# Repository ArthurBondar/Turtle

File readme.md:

# Underwater Camera Project
Underwater Point of View Camera is designed for marine data collection applications. The primary goal of this project is to aid fisheries and biologist with underwater video collection.

## Features:
* 300m dept rated enclosure
* HD (1080p 30fps) video recording
* GPS location tracking
* 3-5 days battery run time ( 8hr recording per day )
* Ability to interface with various sensors

### Underwater Camera
This unit is designed to use as Point-of-view camera tag for Leatherback turtle studies. The unit features a GPS and a small power-efficient computer. The collected is stored on a microSD card.

### Line Camera
This unit is designed for stationary monitoring application used by fisheries. GPS module is optional for this system. The collected data is stored on a USB flash drive.

### Software Tools
Windows Programs for working with the unit:
* FFMPEG YAG - software for converting cameras native h264 video format to mp4
* Win32 Disk Imager - program for reading and writiing software to the unit

### System Images
Software packages are avaiable on Google Drive:
* Underwater / Line Camera Software Image: https://drive.google.com/file/d/10pP7cINGF-45ElwvxjcI6ze0uSWwasvH/view?usp=sharing

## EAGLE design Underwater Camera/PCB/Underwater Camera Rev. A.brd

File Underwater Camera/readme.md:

## Underwater Camera

### Overview
Underwater Camera Tag is designed for marine data collection. This device can be used as
a POV tag for aquatic turtles. The main interface for the system is a removable USB-flash drive. The on-board computer reads the drive during boot and stores all recorded data on it. During long deployments, more than one day, the Tag is designed to enter sleep mode to extend battery life.

### Operation
During deployment, the Tags computer records video and GPS location at daytime. The main computer shuts down for night-time operation to extend battery life. Recording cycles are handled by a separate microcontroller. Video files, GPS readings, and log file are stored on a removable USB flash drive.

### Main components
* Raspberry Pi + PiCamera 1080p30
* Arduino ProMini (Atmega328)
* Battery Bank + Charger/Boost
* Custom 3D printed parts
* Custom made PCB

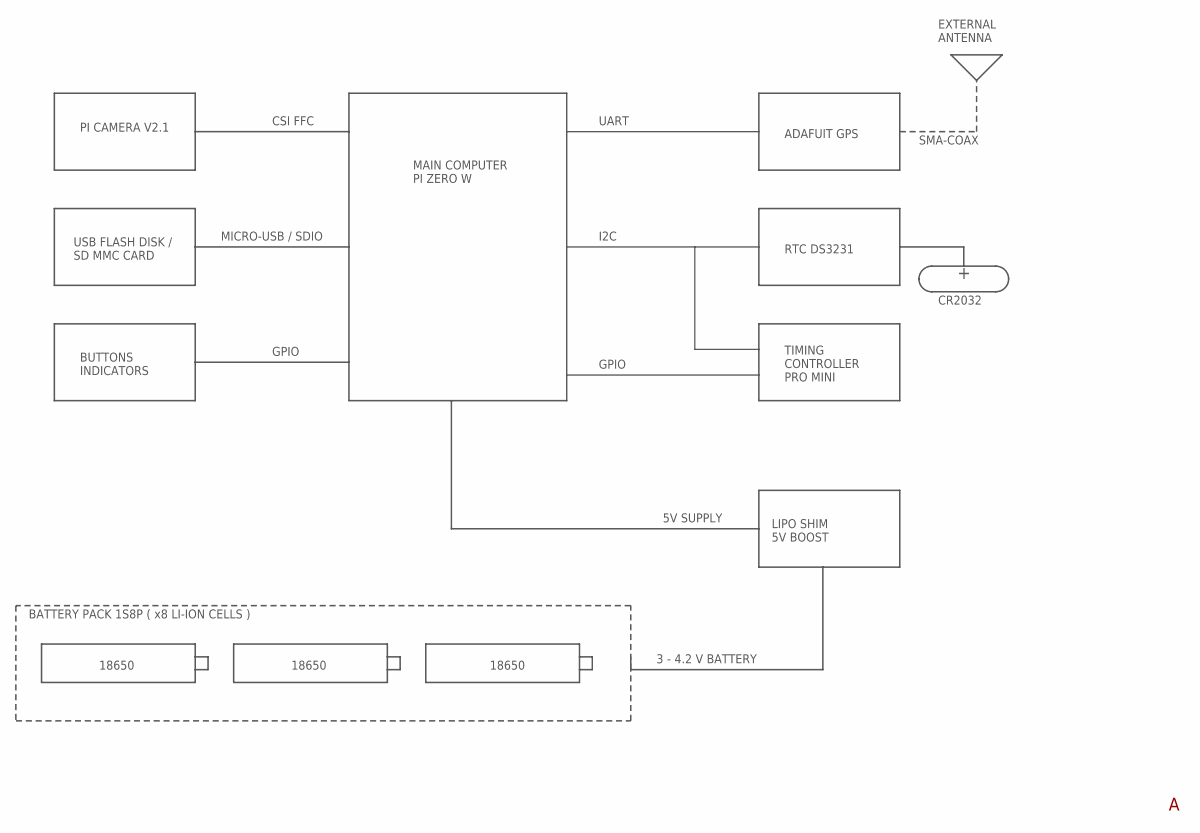
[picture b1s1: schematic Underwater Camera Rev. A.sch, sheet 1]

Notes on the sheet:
BATTERY PACK 1S8P ( x8 LI-ION CELLS )
LIPO SHIM 5V BOOST
MAIN COMPUTER PI ZERO W
TIMING CONTROLLER PRO MINI
PI CAMERA V2.1
USB FLASH DISK / SD MMC CARD
BUTTONS INDICATORS
ADAFUIT GPS
RTC DS3231
GPIO
5V SUPPLY
3 - 4.2 V BATTERY
SMA-COAX
EXTERNAL ANTENNA
18650
CR2032
MICRO-USB / SDIO
CSI FFC
I2C
UART

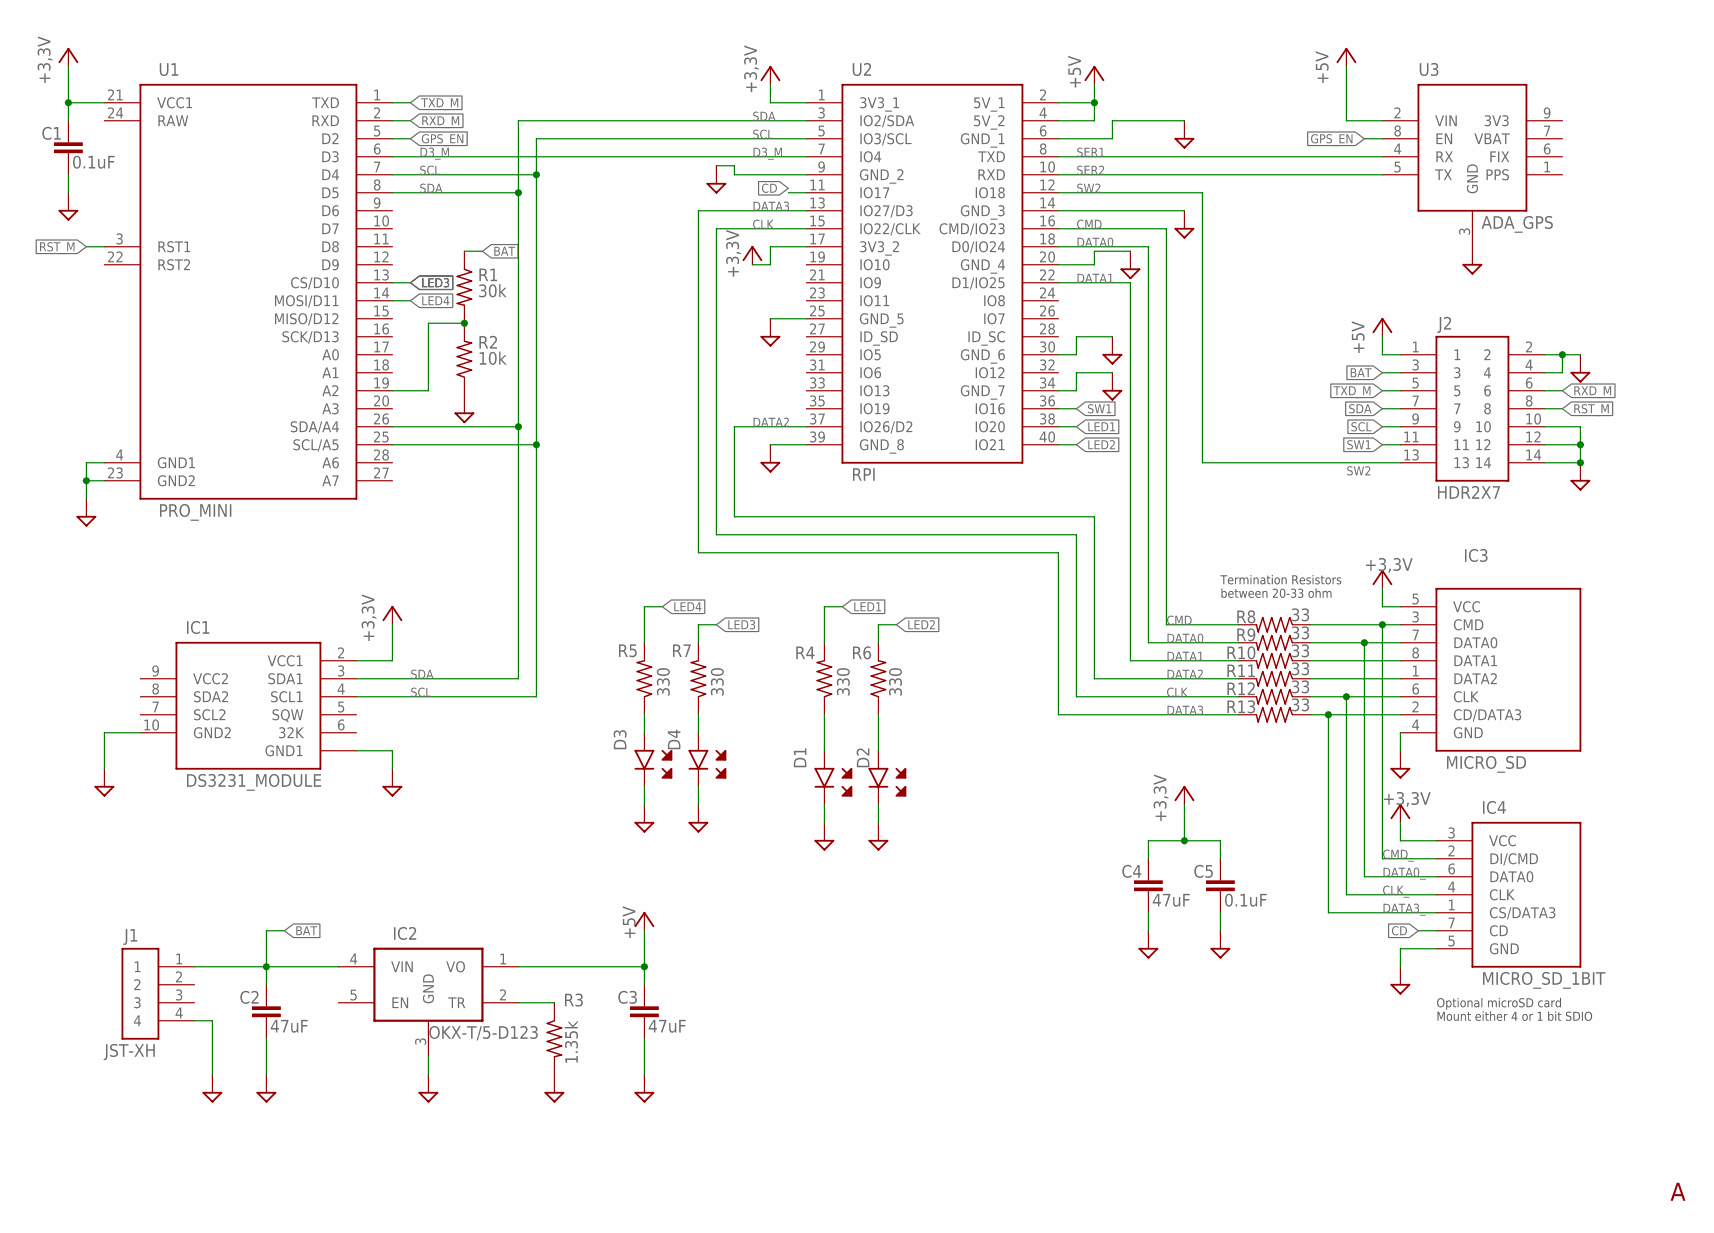
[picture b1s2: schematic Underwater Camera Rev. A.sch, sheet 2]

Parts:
C1, C5: 0.1uF; CAPPRD254W65D300H300B
C2, C3, C4: 47uF; CAPPRD508W65D1000H1100B
D1, D2, D3, D4: LED_THLED-2.54; LEDRD254W60D565H860B
IC1: DS3231_MODULE
IC2: OKX-T/5-D123; OKX-T/5-D12
IC3: MICRO_SD; MICRO_SD_SDIO
IC4: MICRO_SD_1BIT; MICRO_SD_SDIO1B
J1: JST-XH; HDR1X4
J2: HDR2X7
R1: 30k; RESAD1176W63L850D250B
R2: 10k; RESAD1176W63L850D250B
R3: 1.35k; RESAD1176W63L850D250B
R4, R5, R6, R7: 330; RESAD1176W63L850D250B
R8, R9, R10, R11, R12, R13: 33; RESAD1176W63L850D250B
U1: PRO_MINI
U2: RPI; PI_ZERO_W
U3: ADA_GPS; ADA_ULTIMATE_GPS

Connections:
+3,3V: C1.1, C4.1, C5.1, IC1.2 (VCC1), IC3.5 (VCC), IC4.3 (VCC), U1.21 (VCC1), U2.1 (3V3_1), U2.17 (3V3_2)
+5V: C3.1, IC2.1 (VO), J2.1, U2.2 (5V_1), U2.4 (5V_2), U3.2 (VIN)
BAT: C2.1, IC2.4 (VIN), J1.1, J2.3, R1.1
BAT_IN: R1.2, R2.2, U1.19 (A2)
CD: IC4.7 (CD), U2.11 (IO17)
CLK: R12.2, U2.15 (IO22/CLK)
CLK_: IC3.6 (CLK), IC4.4 (CLK), R12.1
CMD: R8.2, U2.16 (CMD/IO23)
CMD_: IC3.3 (CMD), IC4.2 (DI/CMD), R8.1
D3_M: U1.6 (D3), U2.7 (IO4)
DATA0: R9.2, U2.18 (D0/IO24)
DATA0_: IC3.7 (DATA0), IC4.6 (DATA0), R9.1
DATA1: R10.2, U2.22 (D1/IO25)
DATA1_: IC3.8 (DATA1), R10.1
DATA2: R11.2, U2.37 (IO26/D2)
DATA2_: IC3.1 (DATA2), R11.1
DATA3: R13.2, U2.13 (IO27/D3)
DATA3_: IC3.2 (CD/DATA3), IC4.1 (CS/DATA3), R13.1
GND: C1.2, C2.2, C3.2, C4.2, C5.2, D1.2, D2.2, D3.2, D4.2, IC1.1 (GND1), IC1.10 (GND2), IC2.3 (GND), IC3.4 (GND), IC4.5 (GND), J1.4, J2.2, J2.4, J2.10, J2.12, J2.14, R2.1, R3.2, U1.4 (GND1), U1.23 (GND2), U2.6 (GND_1), U2.9 (GND_2), U2.14 (GND_3), U2.20 (GND_4), U2.25 (GND_5), U2.30 (GND_6), U2.34 (GND_7), U2.39 (GND_8), U3.3 (GND)
GPS_EN: U1.5 (D2), U3.8 (EN)
LED1: R4.2, U2.38 (IO20)
LED2: R6.2, U2.40 (IO21)
LED3: R7.2, U1.13 (CS/D10)
LED4: R5.2, U1.14 (MOSI/D11)
unnamed: D4.1, R7.1
unnamed: IC2.2 (TR), R3.1
unnamed: D1.1, R4.1
unnamed: D2.1, R6.1
unnamed: D3.1, R5.1
RST_M: J2.8, U1.3 (RST1)
RXD_M: J2.6, U1.2 (RXD)
SCL: IC1.4 (SCL1), J2.9, U1.7 (D4), U1.25 (SCL/A5), U2.5 (IO3/SCL)
SDA: IC1.3 (SDA1), J2.7, U1.8 (D5), U1.26 (SDA/A4), U2.3 (IO2/SDA)
SER1: U2.8 (TXD), U3.4 (RX)
SER2: U2.10 (RXD), U3.5 (TX)
SW1: J2.11, U2.36 (IO16)
SW2: J2.13, U2.12 (IO18)
TXD_M: J2.5, U1.1 (TXD)

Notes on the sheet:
Termination Resistors between 20-33 ohm
Optional microSD card Mount either 4 or 1 bit SDIO

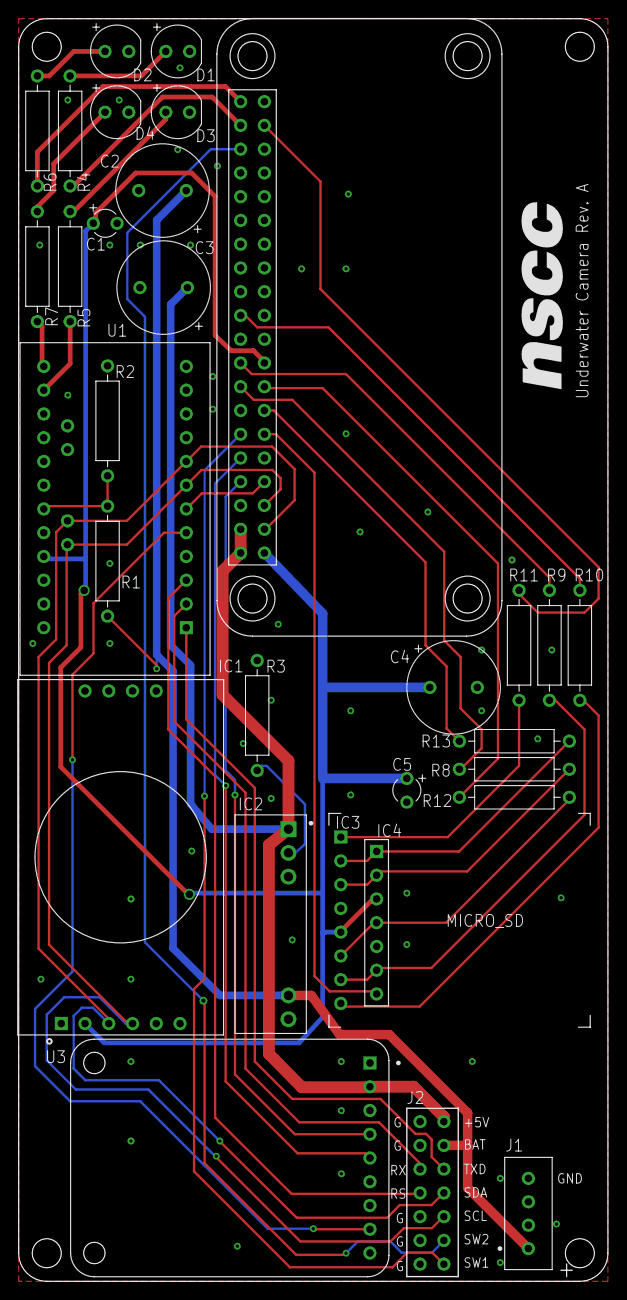
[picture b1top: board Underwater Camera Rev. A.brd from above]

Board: 2 copper layers, 63.0 x 135.0 mm, 31 parts (1 on the bottom side), 38 nets.

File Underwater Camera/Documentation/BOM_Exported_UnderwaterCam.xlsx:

Qty | Value | Device | Parts | Description
2 | 0.1uF | CAP_THCAP-TH-2MM | C1, C5 | Capacitor Electro. TH
1 | 1.35k | RES_THRES-D8.5 | R3 | Resistor TH
1 | 10k | RES_THRES-D8.5 | R2 | Resistor TH
1 | 30k | RES_THRES-D8.5 | R1 | Resistor TH
6 | 33 | RES_THRES-D8.5 | R8, R9, R10, R11, R12, R13 | Resistor TH
4 | 330 | RES_THRES-D8.5 | R4, R5, R6, R7 | Resistor TH
3 | 47uF | CAP_THCAP-ELECTRO-5.08 | C2, C3, C4 | Capacitor Electro. TH
1 | ADA_GPS | ADA_ULTIMATE_GPS9P_BREAKOUT | U3 | Ultimate GPS from Adafruit - Breakout
1 | DS3231_MODULE | DS3231_MODULE | IC1 | DS3231 RTC Breakout Module
1 | HDR2X7 | HDR2X7HDR2X7 | J2
1 | JST-XH | HDR1X4JST-XH | J1 | HEADER 1x4
4 | LED_THLED-2.54 | LED_THLED-2.54 | D1, D2, D3, D4 | TH LED - large
1 | MICRO_SD | MICRO_SD_SNIFFER | IC3 | SparkFun microSD sniffer - breaks out SDIO interface
1 | MICRO_SD_1BIT | MICRO_SD | IC4 | Sparkfun microSD Breakout - SPI/SDIO 1bit accessible
1 | OKX-T/5-D123 | OKX-T/5-D123DMODEL | IC2 | OKX-T/5-D12 by Murata Inc. - Monolithic DC/DC Converter
1 | PI_ZERO | PI_ZERO | U2 | Pi Zero W
1 | PRO_MINI | PRO_MINI | U1 | Arduino Pro Mini from SparkFun 3.3V

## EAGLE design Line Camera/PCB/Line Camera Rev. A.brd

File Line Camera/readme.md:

## Line Camera

### Overview
Line Camera is designed for marine data collection. This device is used in stationary monitoring applications. Camera Tag’s video lapse characteristics can set by the user. The main interface for the system is a removable USB-flash drive. The on-board computer reads the drive during boot and stores all recorded data on it. During long deployments, more than one day, the Tag is designed to enter sleep mode to extend battery life.

### Operation
During deployment, the Tags computer records video during daytime. The main computer shuts down for night-time operation to extend battery life. Recording cycles are handled by a separate microcontroller. Video files, GPS readings, and log file are stored on a removable USB flash drive.

### Main components
* Raspberry Pi + PiCamera 1080p30
* Arduino ProMini (Atmega328)
* Battery Bank + Charger/Boost
* Custom 3D printed parts
* Custom made PCB

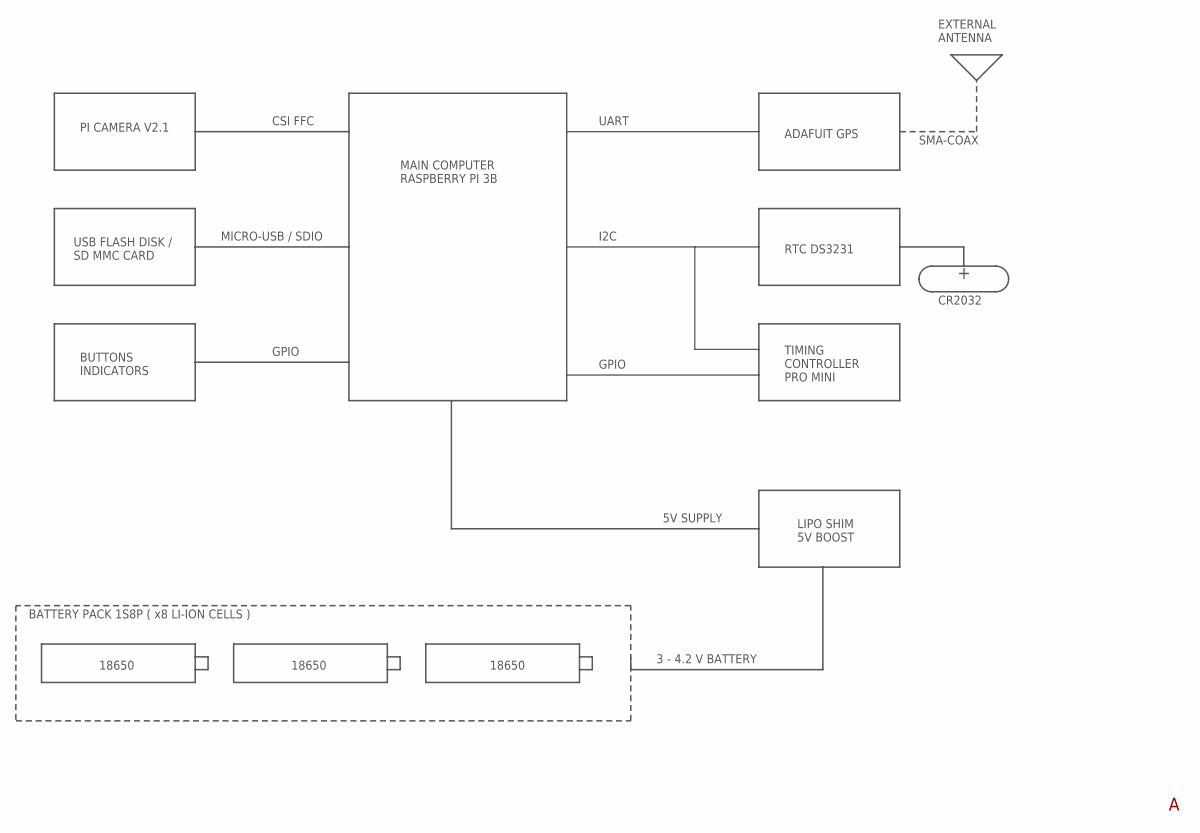
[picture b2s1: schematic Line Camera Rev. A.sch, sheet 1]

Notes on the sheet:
BATTERY PACK 1S8P ( x8 LI-ION CELLS )
LIPO SHIM 5V BOOST
MAIN COMPUTER RASPBERRY PI 3B
TIMING CONTROLLER PRO MINI
PI CAMERA V2.1
USB FLASH DISK / SD MMC CARD
BUTTONS INDICATORS
ADAFUIT GPS
RTC DS3231
GPIO
5V SUPPLY
3 - 4.2 V BATTERY
SMA-COAX
EXTERNAL ANTENNA
18650
CR2032
MICRO-USB / SDIO
CSI FFC
I2C
UART

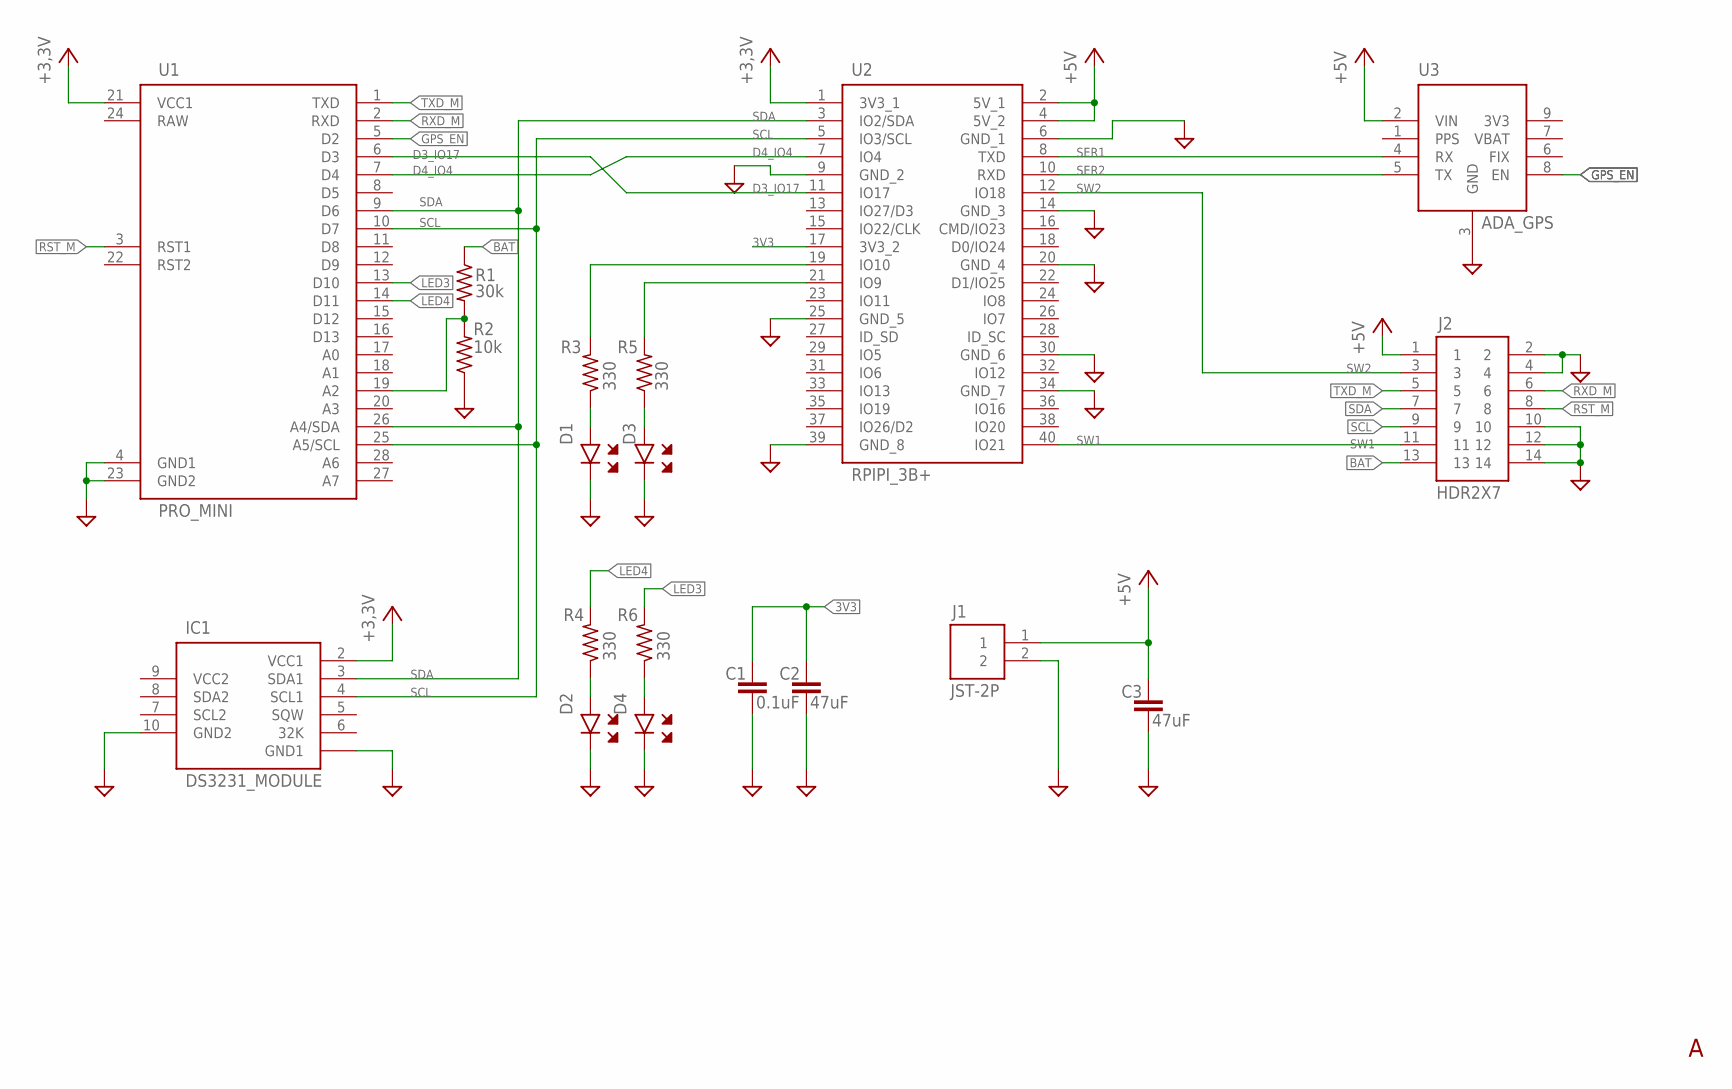
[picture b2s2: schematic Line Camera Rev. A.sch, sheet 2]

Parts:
C1: 0.1uF; CAPPRD254W65D300H300B
C2, C3: 47uF; CAPPRD508W65D1000H1100B
D1, D2, D3, D4: LED_THLED-2.54; LEDRD254W60D565H860B
IC1: DS3231_MODULE
J1: JST-2P; HDR1X2
J2: HDR2X7
R1: 30k; RESAD1176W63L850D250B
R2: 10k; RESAD1176W63L850D250B
R3, R4, R5, R6: 330; RESAD1176W63L850D250B
U1: PRO_MINI
U2: RPIPI_3B+; PI_3B
U3: ADA_GPS; ADA_ULTIMATE_GPS

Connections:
3V3: C1.1, C2.1, U2.17 (3V3_2)
+3,3V: IC1.2 (VCC1), U1.21 (VCC1), U2.1 (3V3_1)
+5V: C3.1, J1.1, J2.1, U2.2 (5V_1), U2.4 (5V_2), U3.2 (VIN)
BAT: J2.13, R1.1
BAT_IN: R1.2, R2.2, U1.19 (A2)
D3_IO17: U1.6 (D3), U2.11 (IO17)
D4_IO4: U1.7 (D4), U2.7 (IO4)
GND: C1.2, C2.2, C3.2, D1.2, D2.2, D3.2, D4.2, IC1.1 (GND1), IC1.10 (GND2), J1.2, J2.2, J2.4, J2.10, J2.12, J2.14, R2.1, U1.4 (GND1), U1.23 (GND2), U2.6 (GND_1), U2.9 (GND_2), U2.14 (GND_3), U2.20 (GND_4), U2.25 (GND_5), U2.30 (GND_6), U2.34 (GND_7), U2.39 (GND_8), U3.3 (GND)
GPS_EN: U1.5 (D2), U3.8 (EN)
LED1: R3.2, U2.19 (IO10)
LED2: R5.2, U2.21 (IO9)
LED3: R6.2, U1.13 (D10)
LED4: R4.2, U1.14 (D11)
unnamed: D4.1, R6.1
unnamed: D1.1, R3.1
unnamed: D3.1, R5.1
unnamed: D2.1, R4.1
RST_M: J2.8, U1.3 (RST1)
RXD_M: J2.6, U1.2 (RXD)
SCL: IC1.4 (SCL1), J2.9, U1.10 (D7), U1.25 (A5/SCL), U2.5 (IO3/SCL)
SDA: IC1.3 (SDA1), J2.7, U1.9 (D6), U1.26 (A4/SDA), U2.3 (IO2/SDA)
SER1: U2.8 (TXD), U3.4 (RX)
SER2: U2.10 (RXD), U3.5 (TX)
SW1: J2.11, U2.40 (IO21)
SW2: J2.3, U2.12 (IO18)
TXD_M: J2.5, U1.1 (TXD)

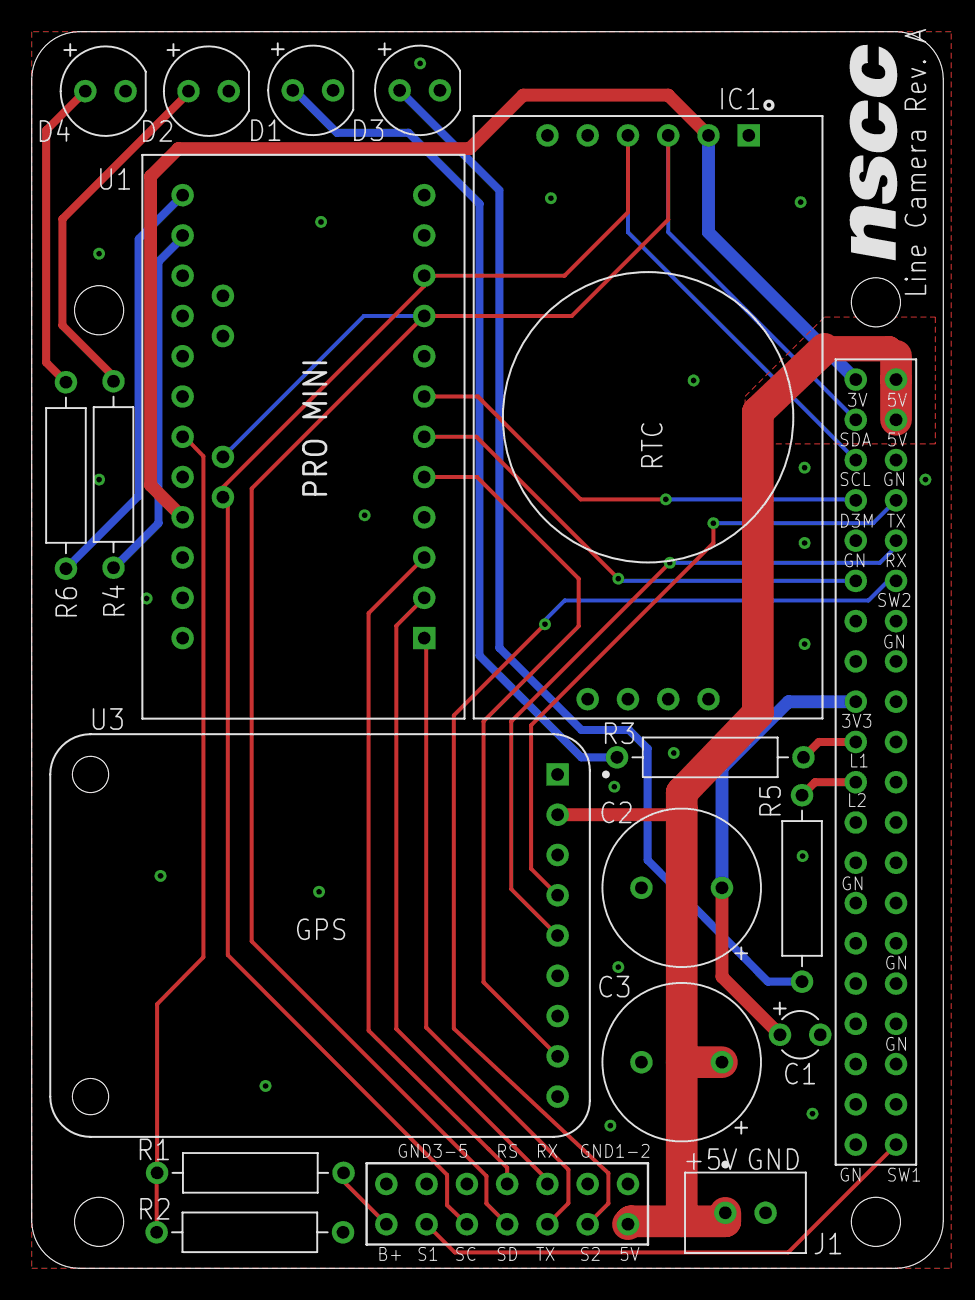
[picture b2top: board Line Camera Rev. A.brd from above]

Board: 2 copper layers, 57.5 x 78.0 mm, 19 parts (1 on the bottom side), 26 nets.

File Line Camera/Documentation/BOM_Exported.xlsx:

Qty | Value | Device | Parts | Description
1 | 0.1uF | CAP_THCAP-TH-2MM | C1 | Capacitor Electro. TH
1 | 10k | RES_THRES-D8.5 | R2 | Resistor TH
1 | 30k | RES_THRES-D8.5 | R1 | Resistor TH
4 | 330 | RES_THRES-D8.5 | R3, R4, R5, R6 | Resistor TH
2 | 47uF | CAP_THCAP-ELECTRO-5.08 | C2, C3 | Capacitor Electro. TH
1 | ADA_GPS | ADA_ULTIMATE_GPS9P_BREAKOUT | U3 | Ultimate GPS from Adafruit - Breakout
1 | DS3231_MODULE | DS3231_MODULE | IC1 | DS3231 RTC Breakout Module
1 | HDR2X7 | HDR2X7HDR2X7 | J2
1 | JST-2P | HDR1X22P2.54MM | J1 | Header 2pin 2.54mm pitch
4 | LED_THLED-2.54 | LED_THLED-2.54 | D1, D2, D3, D4 | TH LED - large
1 | PRO_MINI | PRO_MINI | U1 | Arduino Pro Mini from SparkFun 3.3V
1 | RPIPI_3B+ | RPIPI_3B+ | U2 | Pi Header with different package variations

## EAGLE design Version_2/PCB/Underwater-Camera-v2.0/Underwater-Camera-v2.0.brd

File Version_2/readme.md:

## Underwater POV Camera Tag V2.0

### Overview
The Underwater Camera unit is designed for marine data collection. The tag is geared for video recording and GPS data collection, as well as sensor data logging. This device can be used as a POV camera for aquatic turtles, or in stationary monitoring applications. The tags operating parameters are configured through a web user interface. 
### Operation
When deployed, the unit records video data during daytime and shuts down at night to extend battery life. A separate microcontroller handles recording cycles. Video files, GPS readings, and log file are stored on a removable USB flash drive.
### Main components
* Single Board Computer (Raspberry Pi Zero W) 
* Digital HD Camera 1080p30 (PiCamera v2.1)
* Microprocessor (ATMega328p)
* GPS module + Antenna
* Battery Bank (6/8 Lithium-ion cells)
* Custom 3D printed parts
* 3" Enclosure from BlueRobotics
* Custom made PCB

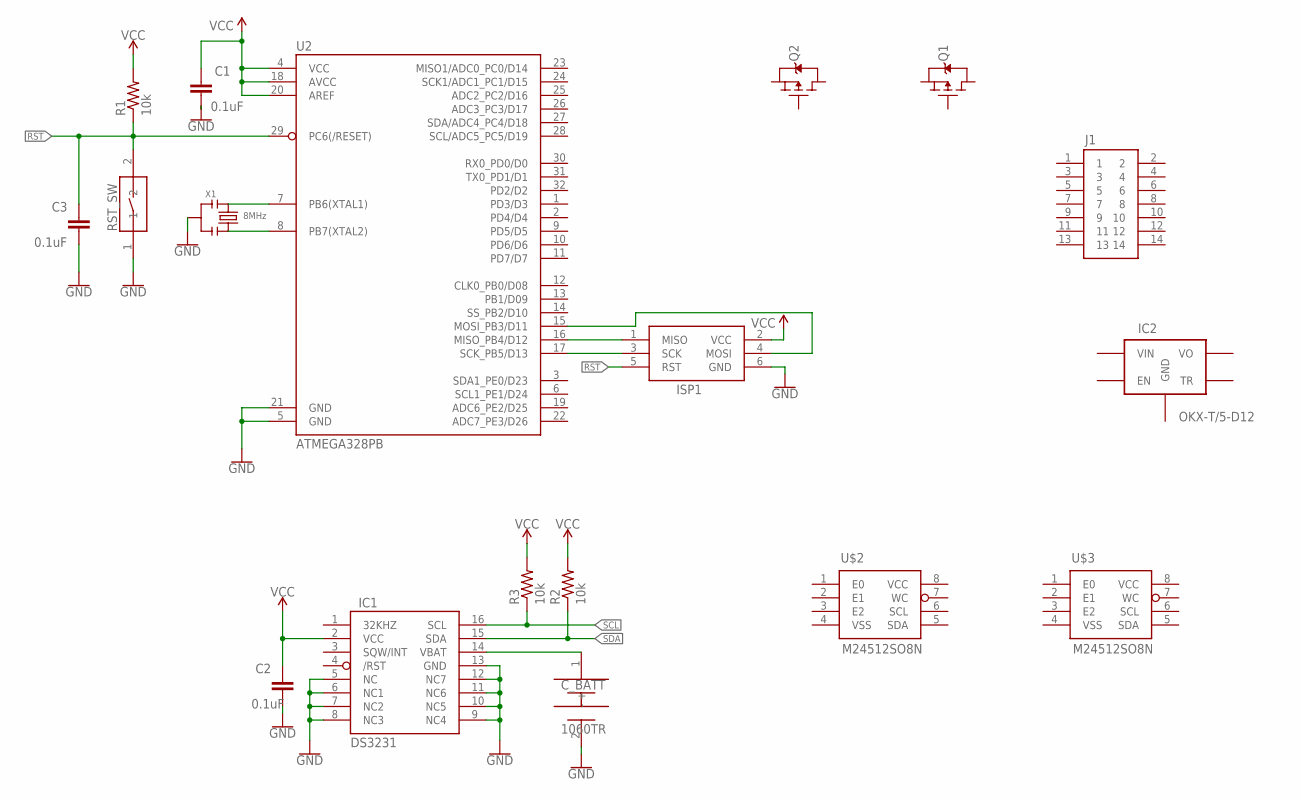
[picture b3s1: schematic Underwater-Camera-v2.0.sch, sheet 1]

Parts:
C1, C2, C3: 0.1uF; CAPC1608X50
C_BATT: 1060TR; RESC26736X10
IC1: DS3231SOIC-16; SOIC127P1135X265-16
IC2: OKX-T/5-D12; HDRV9W64P254_1X9_2290X508X838B
ISP1: AVR_ISPHDR2X3; HDRV6W64P254_2X3_1016X508X838B
J1: HDR2X7HDR2X7; HDRV14W64P254_2X7_1778X508X838B
Q1, Q2: DMG2305UXSOT23; SOT95P240X110-3
R1, R2, R3: 10k; RESC1608X50
RST_SW: SWITCHB3U-1000P; BEADC4225X160
U2: ATMEGA328PB; QFP80P900X900X120-32
U$2, U$3: M24512SO8N; SOIC127P600X175-8
X1: 8MHz; RESCAXE120P320X130X70-6

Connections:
GND: C1.2, C2.2, C3.2, C_BATT.2 (-), IC1.5 (NC), IC1.6 (NC1), IC1.7 (NC2), IC1.8 (NC3), IC1.9 (NC4), IC1.10 (NC5), IC1.11 (NC6), IC1.12 (NC7), IC1.13 (GND), ISP1.6 (GND), RST_SW.1, U2.5 (GND), U2.21 (GND), X1.2, X1.5 (2)
unnamed: U2.7 (PB6(XTAL1)), X1.1, X1.6 (1)
unnamed: U2.8 (PB7(XTAL2)), X1.3, X1.4 (3)
unnamed: ISP1.3 (SCK), U2.17 (SCK_PB5/D13)
unnamed: ISP1.1 (MISO), U2.16 (MISO_PB4/D12)
unnamed: ISP1.4 (MOSI), U2.15 (MOSI_PB3/D11)
unnamed: C_BATT.1 (+), IC1.14 (VBAT)
RST: C3.1, ISP1.5 (RST), R1.1, RST_SW.2, U2.29 (PC6(/RESET))
SCL: IC1.16 (SCL), R3.1
SDA: IC1.15 (SDA), R2.1
VCC: C1.1, C2.1, IC1.2 (VCC), ISP1.2 (VCC), R1.2, R2.2, R3.2, U2.4 (VCC), U2.18 (AVCC), U2.20 (AREF)

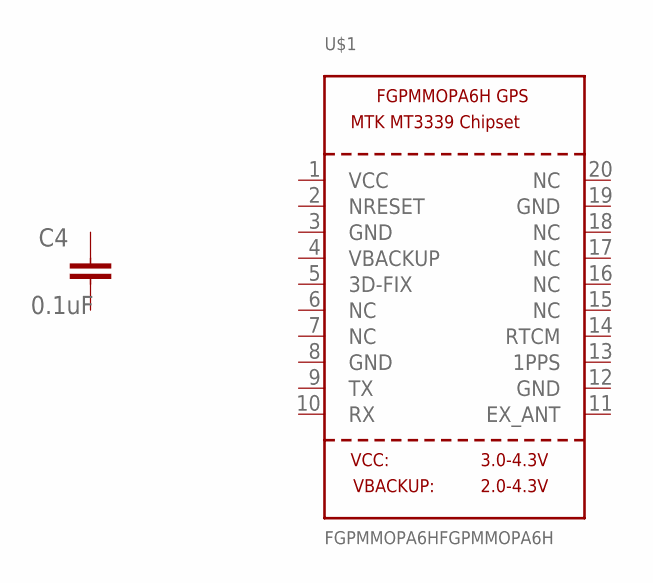
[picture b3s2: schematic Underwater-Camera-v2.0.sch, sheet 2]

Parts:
C4: 0.1uF; CAPC1608X50
U$1: FGPMMOPA6HFGPMMOPA6H; SON150P1800X1800X500-20

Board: 2 copper layers, 20 parts (0 on the bottom side), 11 nets, no tracks yet.

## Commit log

2018-07-01 June 30, 2018 (PCB and 3D parts added)
2018-07-31 July30/18-Added US version (not tested/finished)
2018-08-01 July 30/18 US version code added, parser partially tested, not on Win
2018-10-07 Oct 7, 2018-Work in progress
2018-10-08 Oct 8, 2018 - v3.2 partially tested
2018-10-09 Oct 9, 2018 - Added CPU parameter logging
2018-10-10 Oct 10, 2018 - Current Release v3.2 System1
2018-10-13 13/10/2018-Documentation Added
2018-10-23 Added Image
2018-10-23 image fixed
2018-10-23 trying the image
2018-10-23 Adding image
2018-11-08 08/11/2018 Clean up and documentation
2018-11-08 New Documentation
2019-07-18 the first commit
2019-08-23 camera software partially tested
2019-08-23 added images
2019-08-28 adjusted the software to work with both boards
2019-09-05 Line camera software tested
2019-09-15 Underwater Camera release 1

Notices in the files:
parts and their libraries:
SparkFun-PowerSymbols: Licensing: Creative Commons ShareAlike 4.0 International - https://creativecommons.org/licenses/by-sa/4.0
